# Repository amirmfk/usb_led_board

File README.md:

# usb_led_board
USB Powered Led Controller Board

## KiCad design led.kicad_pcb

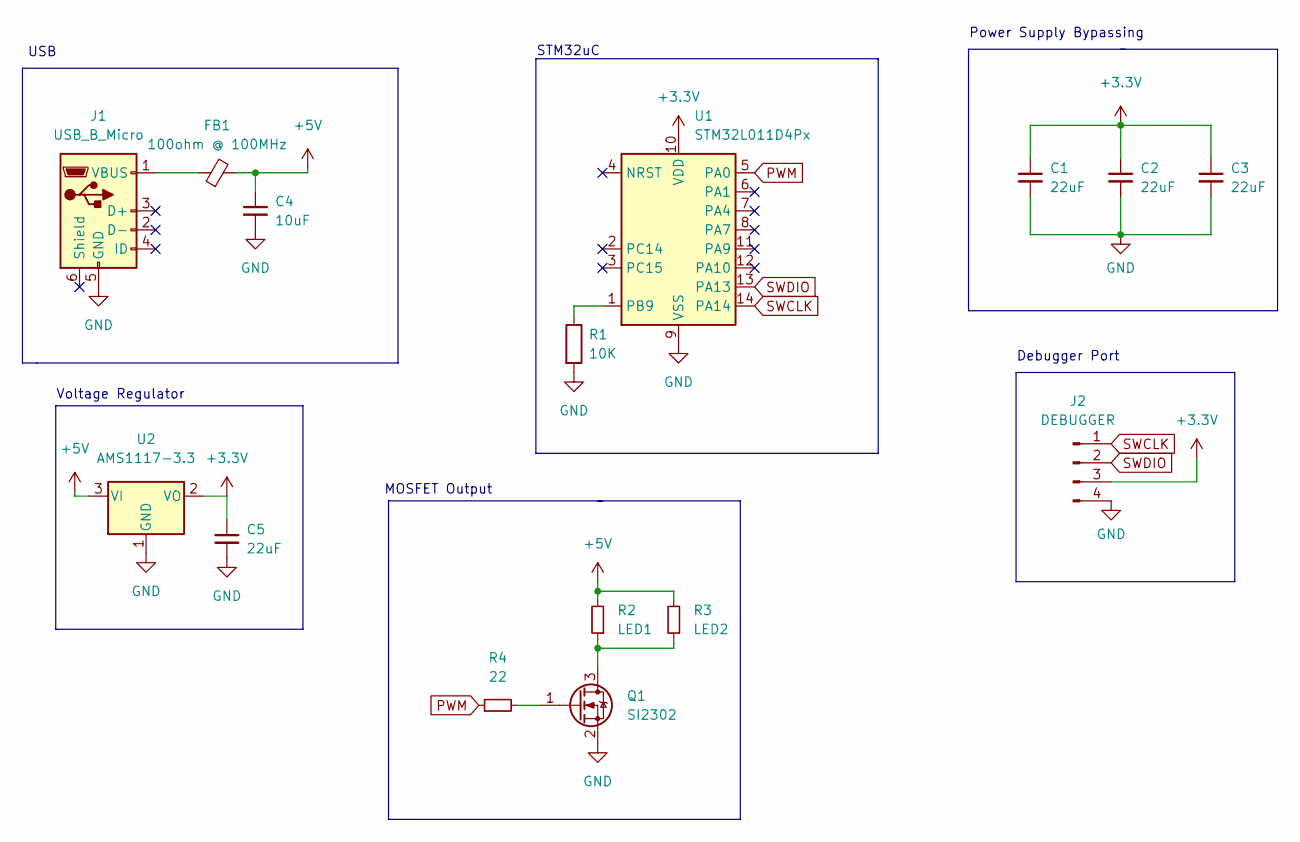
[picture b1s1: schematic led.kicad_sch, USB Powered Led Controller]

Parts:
C1, C2, C3, C5: 22uF; C_0603_1608Metric
C4: 10uF; C_0603_1608Metric
FB1: 100ohm @ 100MHz; L_0805_2012Metric
J1: USB_B_Micro; USB_Micro-B_Molex_47346-0001
J2: DEBUGGER; PinHeader_1x04_P1.27mm_Vertical
Q1: SI2302; SOT-23
R1: 10K; R_0402_1005Metric
R2: LED1; R_0805_2012Metric
R3: LED2; R_0805_2012Metric
R4: 22; R_1206_3216Metric
U1: STM32L011D4Px; TSSOP-14_4.4x5mm_P0.65mm
U2: AMS1117-3.3; SOT-223-3_TabPin2

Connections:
+3V3: C1.1, C2.1, C3.1, C5.1, J2.3, U1.10 (VDD), U2.2 (VO)
+5V: C4.1, FB1.2, R2.2, R3.2, U2.3 (VI)
GND: C1.2, C2.2, C3.2, C4.2, C5.2, J1.5 (GND), J2.4, Q1.2 (S), R1.2, U1.9 (VSS), U2.1 (GND)
unnamed: FB1.1, J1.1 (VBUS)
unnamed: Q1.1 (G), R4.2
unnamed: Q1.3 (D), R2.1, R3.1
unnamed: R1.1, U1.1 (PB9)
PWM: R4.1, U1.5 (PA0)
SWCLK: J2.1, U1.14 (PA14)
SWDIO: J2.2, U1.13 (PA13)

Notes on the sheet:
MOSFET Output
Debugger Port
Voltage Regulator
Power Supply Bypassing
USB
STM32uC

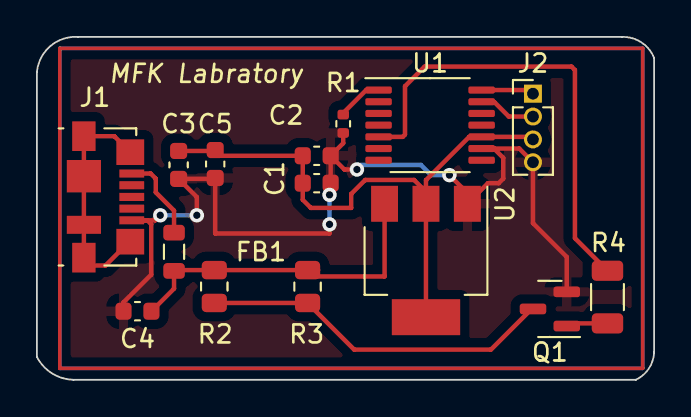
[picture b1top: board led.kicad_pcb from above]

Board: 2 copper layers, 34.3 x 19.1 mm, 15 parts (0 on the bottom side), 10 nets.
